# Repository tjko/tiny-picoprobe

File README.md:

# tiny-picoprobe

Tiny PicoProbe is a small PCB to mount Raspberry Pi Pico, when you want to use [PicoProbe](https://github.com/raspberrypi/picoprobe) to debug your [Raspberry Pi Pico](https://www.raspberrypi.com/products/raspberry-pi-pico/) projects without a breadboard...

This was created to make it "handsfree" to update firmware when developing [Fanpico (Smart PWM (PC) Fan Controller)](https://github.com/tjko/fanpico).

If you are not already familiar with PicoProbe see Appendix A in [Getting Started With Pico (PDF)](https://datasheets.raspberrypi.com/pico/getting-started-with-pico.pdf).

There is also tutorial here: [Raspberry Pi Pico and RP2040 - C/C++ Part 2: Debugging with VS Code](https://www.digikey.com/en/maker/projects/raspberry-pi-pico-and-rp2040-cc-part-2-debugging-with-vs-code/470abc7efb07432b82c95f6f67f184c0)

**Update (February 2023)**: There is finally official "picoprobe" available: [Raspberry Pi Debug Probe](https://www.raspberrypi.com/products/debug-probe/).  
which may be better choice if you're looking for ready-made solution. But if you prefer a DIY solution, continue reading...

New Debug Probe makes "tiny-picoprobe" look not so small anymore:

## PCB
PCB provides pinout to connect to Pico's SWD ("DEBUG") connector with flat (3-pin) ribbon cable, and it also has pinouts for UART and powering the Pico being programmed/debugged.

Designed with [KiCad](https://www.kicad.org/) 6.0.  PCB allows mounting Pico directly or using headers:

## Kerbers
Kerber files ready to be sent to a PCB maker (like JLCPCB, PCBWay, etc...):
* [PCB Version 1.0](kerbers/tiny-picoprobe-v1.zip)
* [PCB Version 1.1](kerbers/tiny-picoprobe-v1.1.zip)

You will only need the ZIP file (link above) to order PCBs. Simply upload the ZIP file to a PCB maker website. Then you typically only need to only select quantity and PCB color. If ordering from JLCPCB you can also choose to "Specify a location" in the Remove Order Number option (this will place order number on the PCB so that the Pico will cover it).

## Assembly
PCB contains footprints for a 0805 size SMD LED and resistor to provide power indicator. Power indicator is optional.

ID|Type|Description|Mouser P/N|LCSC P/N
--|----|-----------|----------|---------
D1|LED (0805)|Pad is suitable for handsoldering 0805 size LEDs, 0603 should work as well...|710-150080GS75000 (?)|C434432
R1|7.5k (0805)|Depending on LED used choose appropriate resistor. Green high-intensity 0805 LEDs typically work nicely with resistor in 5k to 10k range|603-RC0805FR-077K5L|C229003

Note, if soldering Pico directly on the PCB, then 1" diameter shrink tubing can be used to wrap the pico and PCB in nice insulated package.

## DIY Kits

If you'd like to support Open Source Hardware development.  DIY Kits are made available in limited quantity.

Check availability here: [eBay](https://www.ebay.com/usr/oh6lxv)

## Credits
Idea for this PCB came from [Fabien-Chouteau/picoprobe-pcb](https://github.com/Fabien-Chouteau/picoprobe-pcb) (check his version as he sells it on Tindie).

KiCad Pico model/footprint that was used can be found here [ncarandini/KiCad-RP-Pico](https://github.com/ncarandini/KiCad-RP-Pico)

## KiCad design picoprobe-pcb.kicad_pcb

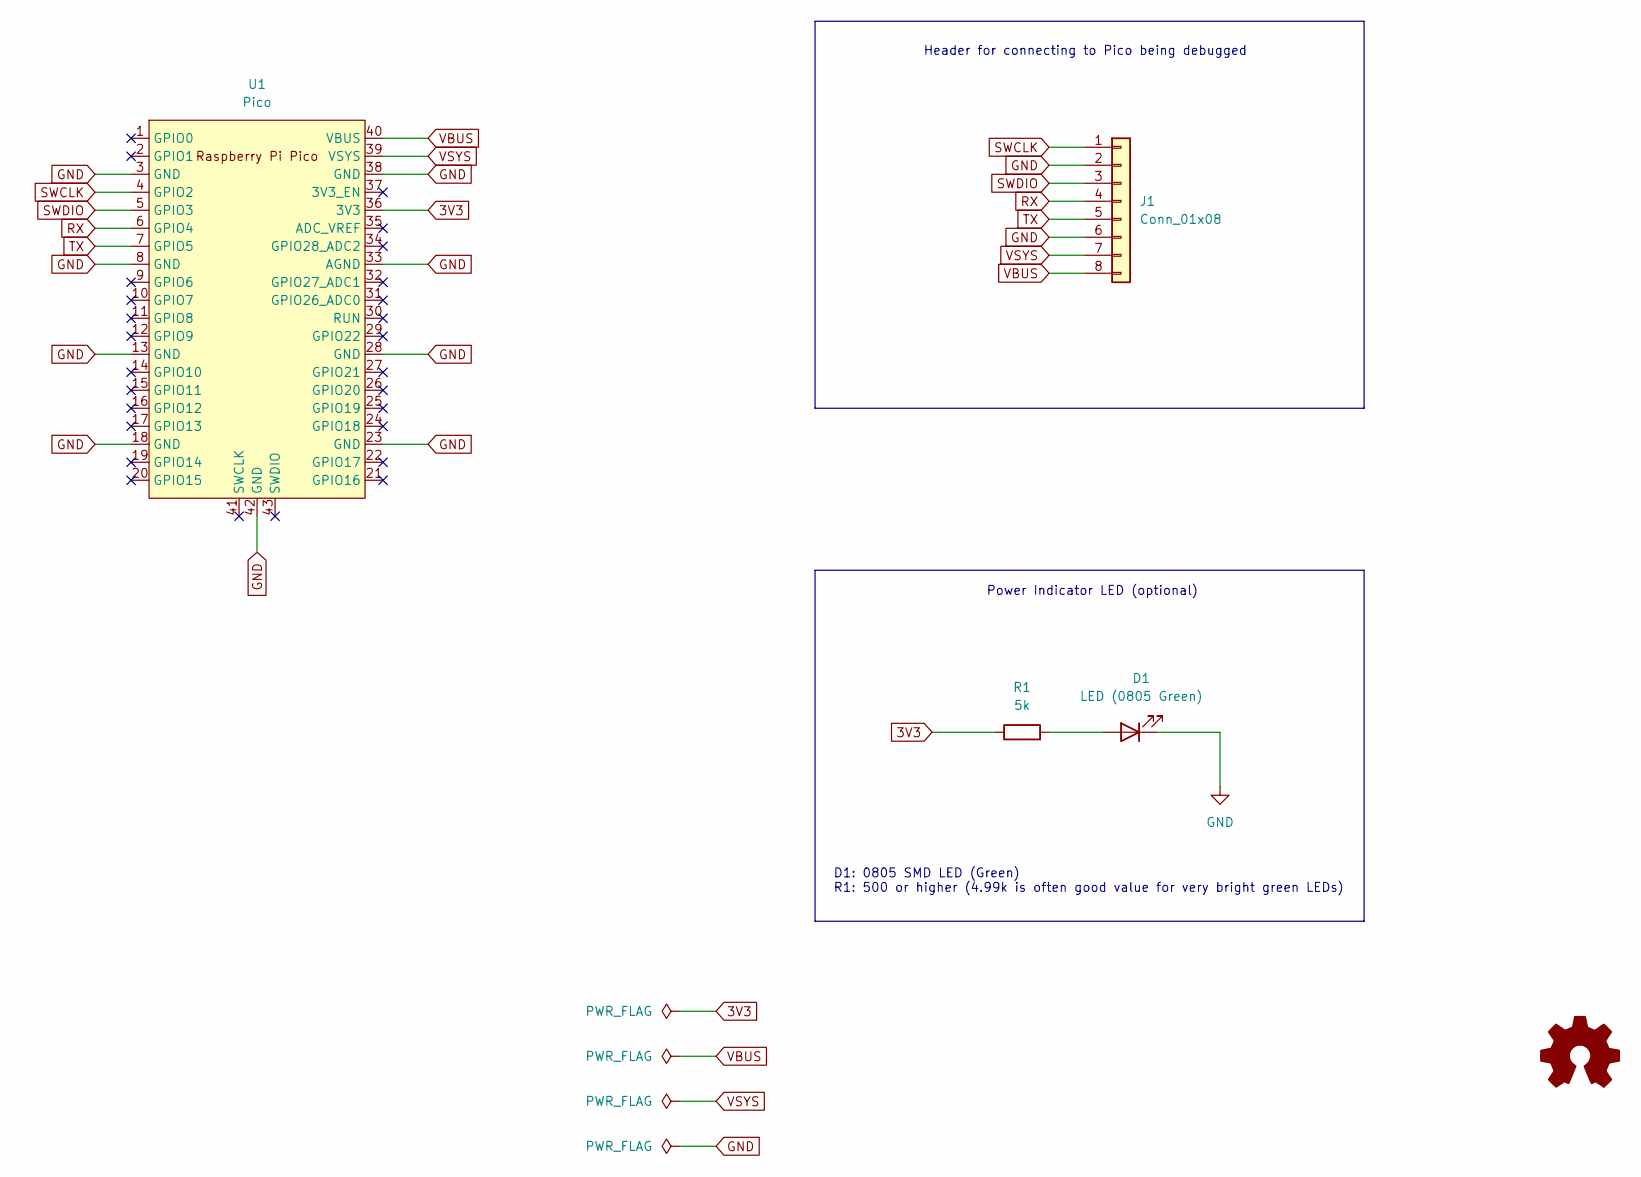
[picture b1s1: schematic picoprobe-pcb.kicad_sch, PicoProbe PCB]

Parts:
D1: LED (0805 Green); LED_0805_2012Metric_Pad1.15x1.40mm_HandSolder
J1: Conn_01x08; PinHeader_1x08_P2.54mm_Vertical
R1: 5k; R_0805_2012Metric_Pad1.20x1.40mm_HandSolder
U1: Pico; RPi_Pico_SMD_TH

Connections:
3V3: R1.1, U1.36 (3V3)
GND: D1.1 (K), J1.2, J1.6, U1.3 (GND), U1.8 (GND), U1.13 (GND), U1.18 (GND), U1.23 (GND), U1.28 (GND), U1.33 (AGND), U1.38 (GND), U1.42 (GND)
unnamed: D1.2 (A), R1.2
RX: J1.4, U1.6 (GPIO4)
SWCLK: J1.1, U1.4 (GPIO2)
SWDIO: J1.3, U1.5 (GPIO3)
TX: J1.5, U1.7 (GPIO5)
VBUS: J1.8, U1.40 (VBUS)
VSYS: J1.7, U1.39 (VSYS)

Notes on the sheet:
Header for connecting to Pico being debugged
D1: 0805 SMD LED (Green) R1: 500 or higher (4.99k is often good value for very bright green LEDs)
Power Indicator LED (optional)

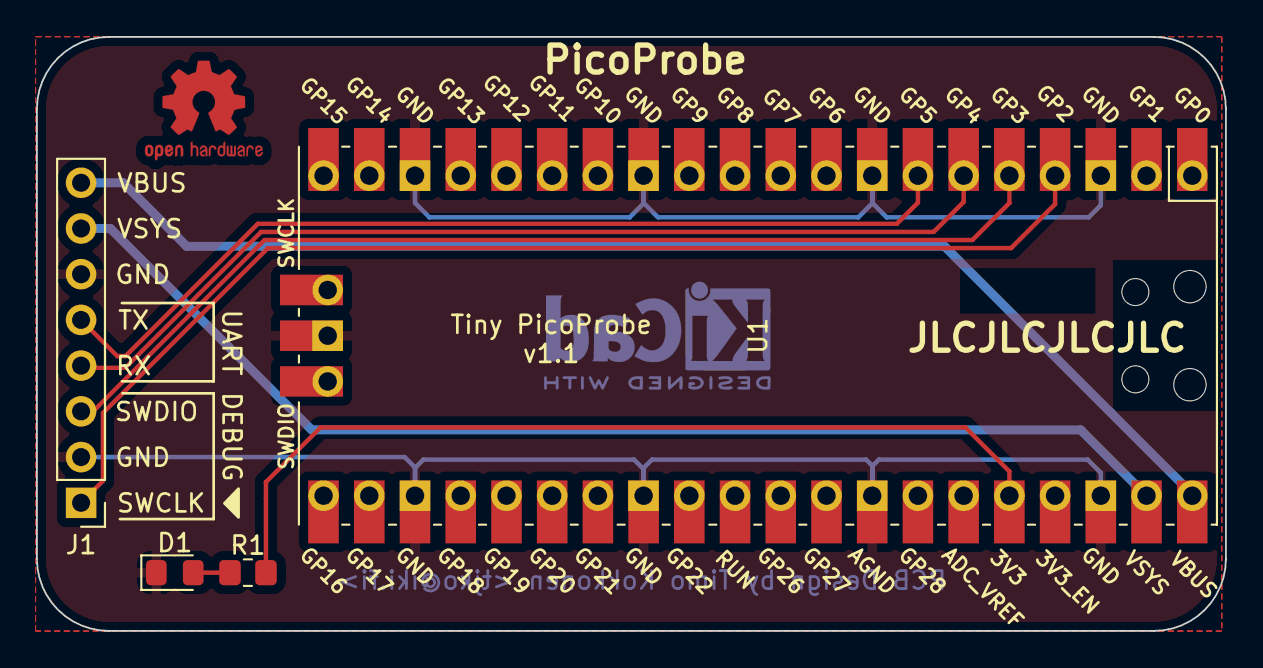
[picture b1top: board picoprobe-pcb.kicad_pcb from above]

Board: 2 copper layers, 66.1 x 33.0 mm, 4 parts (0 on the bottom side), 9 nets.

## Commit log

2022-02-05 Add render of the pcb.
2022-02-05 Initial board version.
2022-02-26 Add photos of the first units built.
2022-02-26 Slightly improved PCB v1.1 and kerbers.
2022-02-26 Ignore MacOS stuff.
2022-02-27 Added render of the PCB.
2022-10-14 Add photo of shrinkwrapped board.
2023-02-25 added size comparison picture
